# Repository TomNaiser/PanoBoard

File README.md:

# PanoBoard
Integrated Electronics Board for a Gigapixel Panorama Head (pan and tilt motion)
-Arduino nano based controller
-bluetooth communication with the windowsbased control notebook
-PID position control (modified RC-Servos)
-rotatory position encoders for precise position control 

The latest version PanoBoardV5 is a size-reduced version. With the shrunken electronics box the panorama rig fits into my photo backpack. 

## Arduino Nano R4 upgrade

The [PanoBoard V5 Nano R4 patch](PanoBoard5KiCad/Nano-R4-Patch.md) explains the resistor changes, GPIO current limits, encoder I²C pull-ups, power supply and firmware porting needed to replace the classic Nano with a Nano R4. The KiCad files remain the original V5 design; apply the documented rework before operating the R4.

Current software: [PanoDuinoControl firmware](https://github.com/TomNaiser/PanoDuinoControl), [Android app and system documentation](https://github.com/TomNaiser/PanoramaSoftware), and [PanoramaControl for Windows](https://github.com/TomNaiser/PanoramaControl).

Warning! The circuits in this project were designed as a hobbyist project and may contain unintentional mistakes.  I don't take any responsibility for damages caused by using the above circuit design. Please use the provided information at your own risk!

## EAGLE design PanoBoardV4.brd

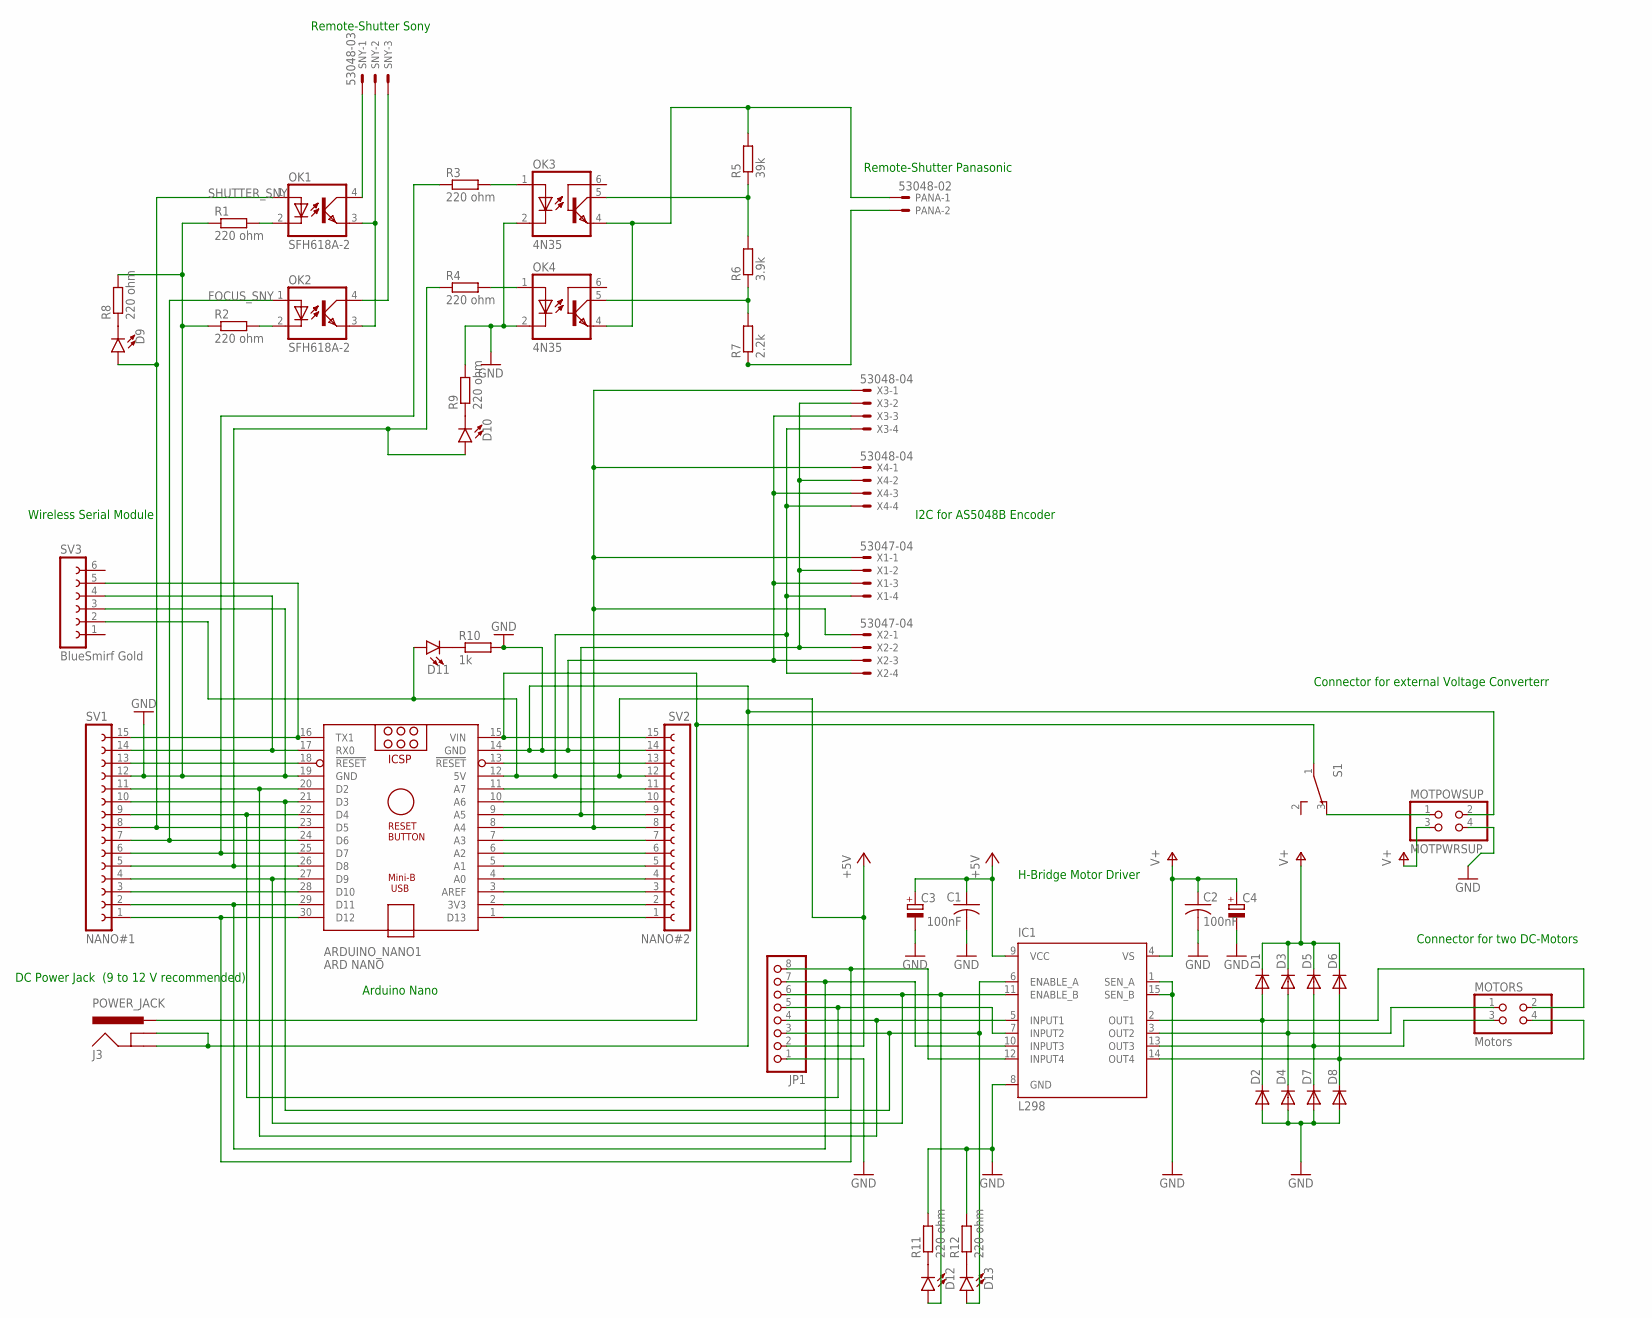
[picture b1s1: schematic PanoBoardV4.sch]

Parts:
ARDUINO_NANO1: ARD NANO; ARDUINO_NANO
C1, C2: 100nF; C050-024X044
C3, C4: CPOL-EUE3.5-10; E3,5-10
D1, D2, D3, D4, D5, D6, D7, D8: DIODE-D-5; D-5
D9, D10, D11, D12, D13: LED1206; LED-1206
IC1: L298; MULTIWATT-15
J3: POWER_JACK; POWER_JACK_PTH
JP1: PINHD-1X8; 1X08
MOTORS: Motors; 2X02
MOTPOWSUP: MOTPWRSUP; 2X02
OK1, OK2: SFH618A-2; DIP4
OK3, OK4: 4N35; DIL06
PANA: 53048-02
R1, R2, R3, R4, R8, R9, R11, R12: 220 ohm; R1210
R5: 39k; R1210
R6: 3.9k; R1210
R7: 2.2k; R1210
R10: 1k; R1210
S1: 450302014072
SNY: 53048-03
SV1: NANO#1; FE15
SV2: NANO#2; FE15
SV3: BlueSmirf Gold; FE06W
X1, X2: 53047-04
X3, X4: 53048-04

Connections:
+5V: ARDUINO_NANO1.12 (5V), C1.1, C3.+, D11.A, IC1.9 (VCC), JP1.2, SV2.12, SV3.2, X1.4, X2.4, X3.4, X4.4
FOCUS_SNY: ARDUINO_NANO1.24 (D6), OK2.1 (A), SV1.7
GND: ARDUINO_NANO1.14 (GND), ARDUINO_NANO1.19 (GND), C1.2, C2.2, C3.-, C4.-, D2.A, D4.A, D7.A, D8.A, IC1.1 (SEN_A), IC1.8 (GND), IC1.15 (SEN_B), J3.GND, J3.GNDBREAK, JP1.1, MOTPOWSUP.2, MOTPOWSUP.4, OK3.2 (C), OK4.2 (C), R1.1, R2.1, R8.2, R9.2, R10.2, R11.2, R12.2, SV1.12, SV2.14, SV3.3, X1.3, X2.3, X3.3, X4.3
unnamed: ARDUINO_NANO1.16 (TX1), SV1.15, SV3.5
unnamed: ARDUINO_NANO1.17 (RX0), SV1.14, SV3.4
unnamed: ARDUINO_NANO1.18 (!RESET), SV1.13
unnamed: OK1.2 (C), R1.2
unnamed: ARDUINO_NANO1.20 (D2), IC1.5 (INPUT1), JP1.4, SV1.11
unnamed: ARDUINO_NANO1.21 (D3), D13.A, IC1.6 (ENABLE_A), JP1.3, SV1.10
unnamed: ARDUINO_NANO1.22 (D4), IC1.7 (INPUT2), JP1.5, SV1.9
unnamed: OK1.3 (EMIT), OK2.3 (EMIT), SNY.2
unnamed: OK1.4 (COL), SNY.1
unnamed: ARDUINO_NANO1.25 (D7), R3.1, SV1.6
unnamed: ARDUINO_NANO1.26 (D8), D10.A, R4.1, SV1.5
unnamed: ARDUINO_NANO1.27 (D9), D12.A, IC1.11 (ENABLE_B), JP1.6, SV1.4
unnamed: ARDUINO_NANO1.28 (D10), SV1.3
unnamed: ARDUINO_NANO1.29 (D11), IC1.10 (INPUT3), JP1.7, SV1.2
unnamed: ARDUINO_NANO1.30 (D12), IC1.12 (INPUT4), JP1.8, SV1.1
unnamed: ARDUINO_NANO1.15 (VIN), J3.PWR, S1.1, SV2.15
unnamed: OK2.2 (C), R2.2
unnamed: ARDUINO_NANO1.13 (!RESET), SV2.13
unnamed: OK3.1 (A), R3.2
unnamed: ARDUINO_NANO1.11 (A7), SV2.11
unnamed: ARDUINO_NANO1.10 (A6), SV2.10
unnamed: ARDUINO_NANO1.9 (A5), SV2.9, X1.2, X2.2, X3.2, X4.2
unnamed: ARDUINO_NANO1.8 (A4), SV2.8, X1.1, X2.1, X3.1, X4.1
unnamed: ARDUINO_NANO1.7 (A3), SV2.7
unnamed: ARDUINO_NANO1.6 (A2), SV2.6
unnamed: ARDUINO_NANO1.5 (A1), SV2.5
unnamed: ARDUINO_NANO1.4 (A0), SV2.4
unnamed: ARDUINO_NANO1.3 (AREF), SV2.3
unnamed: ARDUINO_NANO1.2 (3V3), SV2.2
unnamed: ARDUINO_NANO1.1 (D13), SV2.1
unnamed: D1.A, D2.C, IC1.2 (OUT1), MOTORS.2
unnamed: D3.A, D4.C, IC1.3 (OUT2), MOTORS.1
unnamed: D6.A, D8.C, IC1.14 (OUT4), MOTORS.4
unnamed: D5.A, D7.C, IC1.13 (OUT3), MOTORS.3
unnamed: OK4.1 (A), R4.2
unnamed: OK2.4 (COL), SNY.3
unnamed: OK3.5 (COL), R5.1, R6.2
unnamed: OK3.4 (EMI), OK4.4 (EMI), PANA.1, R5.2
unnamed: OK4.5 (COL), R6.1, R7.2
unnamed: D9.C, R8.1
unnamed: PANA.2, R7.1
unnamed: D10.C, R9.1
unnamed: D11.C, R10.1
unnamed: MOTPOWSUP.1, S1.3
unnamed: D12.C, R11.1
unnamed: D13.C, R12.1
SHUTTER_SNY: ARDUINO_NANO1.23 (D5), D9.A, OK1.1 (A), SV1.8
V+: C2.1, C4.+, D1.C, D3.C, D5.C, D6.C, IC1.4 (VS), MOTPOWSUP.3

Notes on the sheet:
Remote-Shutter Panasonic
Remote-Shutter Sony
I2C for AS5048B Encoder
H-Bridge Motor Driver
Connector for external Voltage Converterr
Connector for two DC-Motors
Wireless Serial Module
Arduino Nano
DC Power Jack (9 to 12 V recommended)

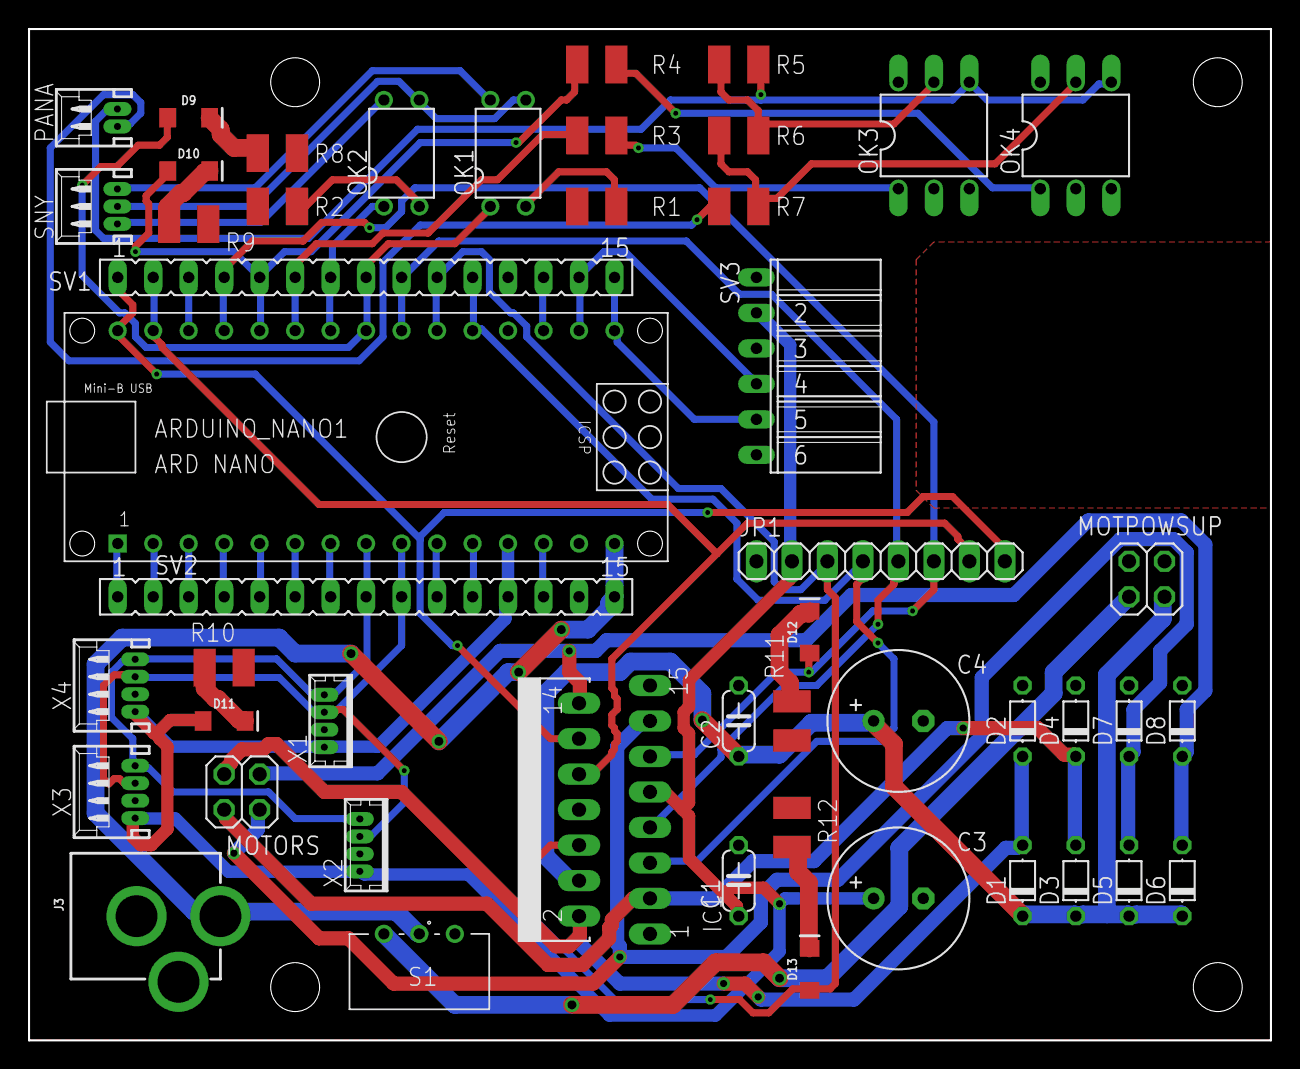
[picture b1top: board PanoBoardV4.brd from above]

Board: 2 copper layers, 88.9 x 72.4 mm, 49 parts (0 on the bottom side), 51 nets.

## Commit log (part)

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2019-05-11 Set theme jekyll-theme-cayman
2019-05-11 Parts List
2023-01-01 PanoBoardV5
    Simplified version of the board. Reduced footprint. Camera Triggering support only the Sony A7
2023-01-01 Photos of the board

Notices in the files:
parts and their libraries:
SparkFun-LED: Licensing: Creative Commons ShareAlike 4.0 International - https://creativecommons.org/licenses/by-sa/4.0
Eagle_SWITCHES: Copyright: Würth Elektronik
